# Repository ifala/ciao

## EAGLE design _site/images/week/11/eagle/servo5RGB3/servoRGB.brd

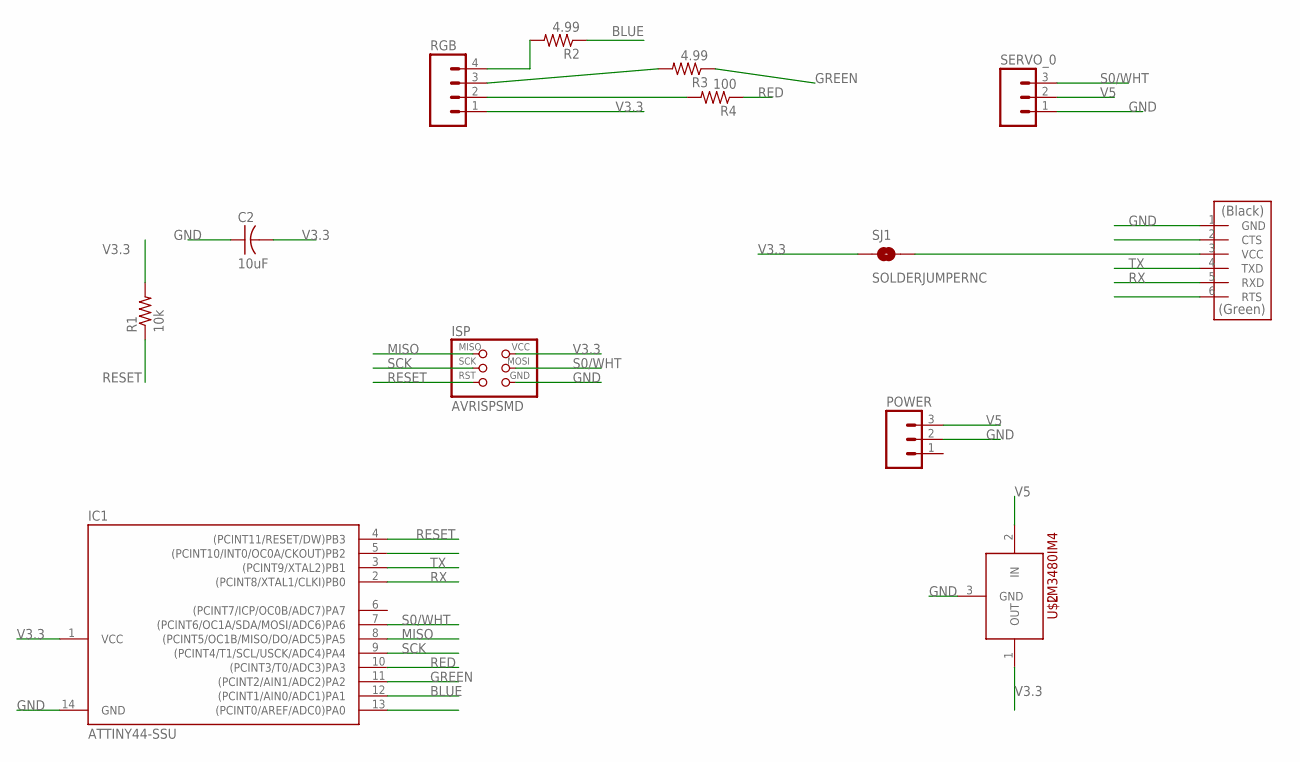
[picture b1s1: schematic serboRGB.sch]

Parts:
C2: 10uF; C1206FAB
IC1: ATTINY44-SSU; SOIC14
ISP: AVRISPSMD; 2X03SMD
POWER: M03SMD_RA_MALE_POST; 1X03_SMD_RA_MALE_POST
R1: 10k; 1206
R2, R3: 4.99; 1206
R4: 100; 1206
RGB: M04SMD; 1X04-SMD
SERVO_0: M03SMD_RA_MALE_POST; 1X03_SMD_RA_MALE_POST
SJ1: SOLDERJUMPERNC; SJ_2S
U$1: FTDI-SMD-HEADER; 1X06SMD
U$2: LM3480IM4; SOT23-3

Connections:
BLUE: IC1.12 ((PCINT1/AIN0/ADC1)PA1), R2.1
GND: C2.1, IC1.14 (GND), ISP.6 (GND), POWER.2, SERVO_0.1, U$1.1 (GND), U$2.3 (GND)
GREEN: IC1.11 ((PCINT2/AIN1/ADC2)PA2), R3.1
MISO: IC1.8 ((PCINT5/OC1B/MISO/DO/ADC5)PA5), ISP.1 (MISO)
unnamed: R4.2, RGB.2
unnamed: R3.2, RGB.3
unnamed: R2.2, RGB.4
unnamed: SJ1.2, U$1.3 (VCC)
RED: IC1.10 ((PCINT3/T0/ADC3)PA3), R4.1
RESET: IC1.4 ((PCINT11/RESET/DW)PB3), ISP.5 (RST), R1.1
RX: IC1.2 ((PCINT8/XTAL1/CLKI)PB0), U$1.5 (RXD)
S0/WHT: IC1.7 ((PCINT6/OC1A/SDA/MOSI/ADC6)PA6), ISP.4 (MOSI), SERVO_0.3
SCK: IC1.9 ((PCINT4/T1/SCL/USCK/ADC4)PA4), ISP.3 (SCK)
TX: IC1.3 ((PCINT9/XTAL2)PB1), U$1.4 (TXD)
V3.3: C2.2, IC1.1 (VCC), ISP.2 (VCC), R1.2, RGB.1, SJ1.1, U$2.1 (OUT)
V5: POWER.3, SERVO_0.2, U$2.2 (IN)

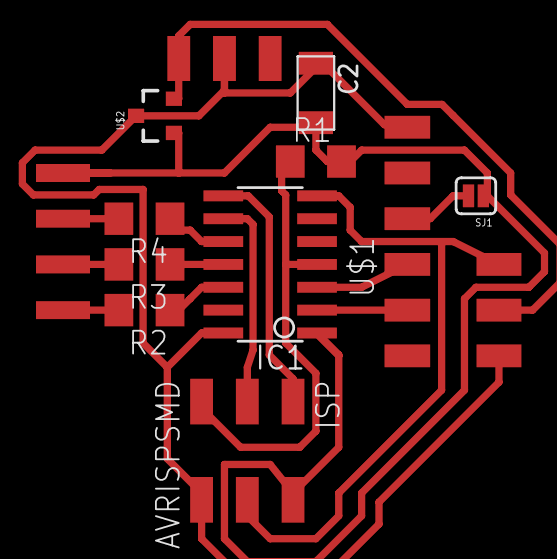
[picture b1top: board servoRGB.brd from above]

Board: 2 copper layers, 13 parts (0 on the bottom side), 16 nets.

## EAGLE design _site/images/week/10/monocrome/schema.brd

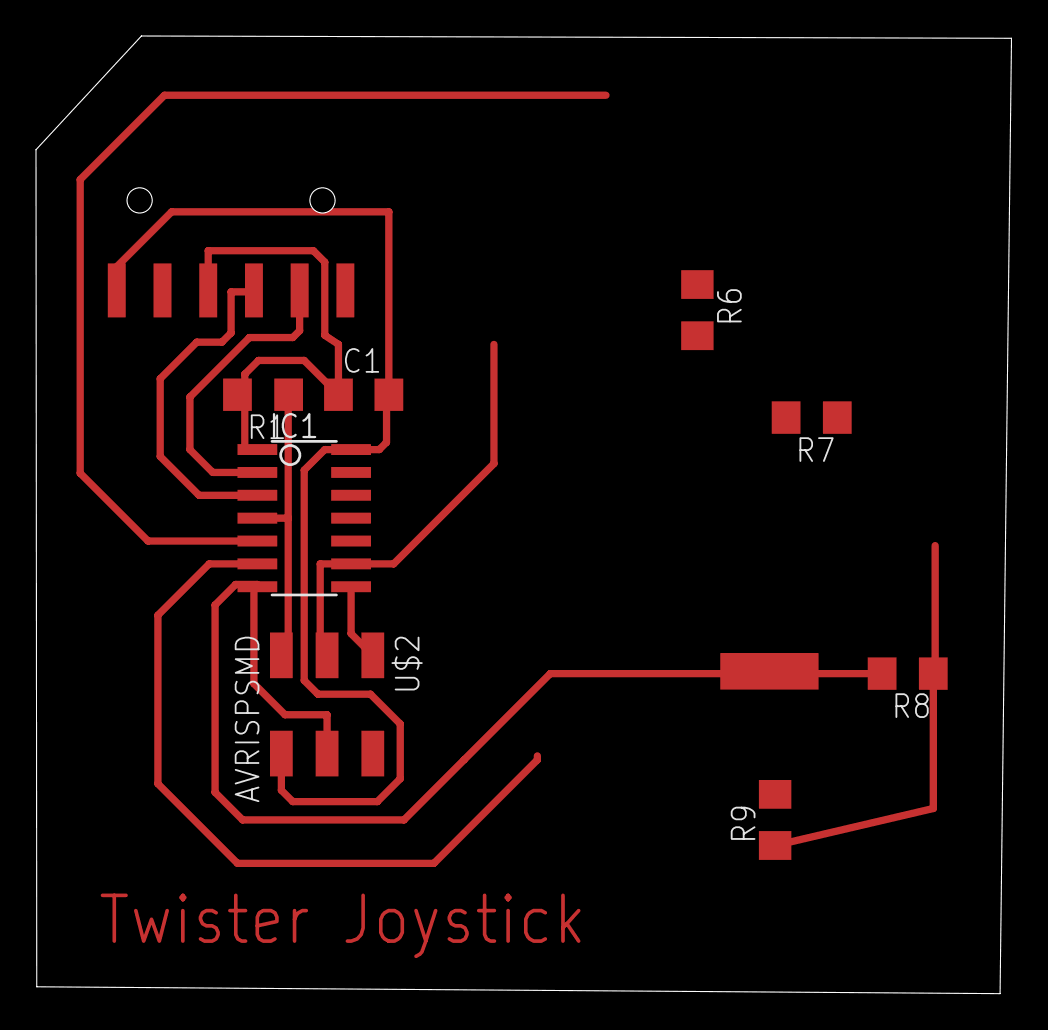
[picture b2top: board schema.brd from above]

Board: 1 copper layer, 54.2 x 53.2 mm, 9 parts (0 on the bottom side), 10 nets.

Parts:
C1: 1uf; C1206
IC1: ATTINY44-SSU; SOIC14
JP1: 1X06-SMD
R1: 10k; R1206
R6, R7, R8, R9: 1M; 1206
U$2: AVRISPSMD; 2X03SMD

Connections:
GND: C1.2, IC1.14, JP1.6, U$2.6
PAD4/SCK: IC1.9, R6.2, U$2.3
PAD5/MISO: IC1.8, R7.2, U$2.1
PAD6/MOSI: IC1.7, R8.2, U$2.4
PAD7: IC1.6, R9.2
RST: IC1.4, R1.1, U$2.5
RX: IC1.2, JP1.2
STEP: IC1.5, R6.1, R7.1, R8.1, R9.1
TX: IC1.3, JP1.3
VCC: C1.1, IC1.1, JP1.4, R1.2

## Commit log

2015-02-10 sito
2015-02-11 add week2
2015-02-11 add illustrator - week2
2015-02-17 news
2015-02-17 localhostremove
2015-02-17 add week3 file
2015-02-17 english
2015-02-19 add start week 4 - mod template
2015-02-19 correct link
2015-02-19 kk mod mobile
2015-02-19 cell
2015-02-24 week 4
2015-02-24 pond - solder
2015-02-24 code indent
2015-02-24 week4 rev1
2015-02-24 week 4 img rsz
2015-03-03 week5 _part1
2015-03-03 week 5 _ 2
2015-03-03 week 5 - update 3
2015-03-04 week 5 up4
2015-03-04 week5 up5
2015-03-10 week 6 update 1
2015-03-10 week 6 update 2
2015-03-10 week 6 update 3
2015-03-10 config
2015-03-18 week 7 _up1
2015-03-18 week 7 up2
2015-03-18 week7 up3
2015-03-18 week 7 up4
2015-03-19 week 7 up5
2015-03-19 week 7 up6
2015-03-19 week 7 up7
2015-03-19 _config error instagram
2015-03-19 correct link week6
2015-03-19 conclusion week7
2015-03-20 week 7 correction
2015-03-24 week 8 up1
2015-03-24 week8 up2
2015-03-25 week8 up3
2015-03-25 add file week 8
2015-03-30 update older assignment
2015-04-01 add google analytics
2015-04-01 revision week1
2015-04-01 revision week1 up2
2015-04-01 week4 up1
2015-04-03 since week8 update
2015-04-06 update link
2015-04-06 update1 week9
2015-04-07 up2 week9
2015-04-07 up3 week9
2015-04-07 up4 week9
2015-04-07 up5 week9
2015-04-07 up6 week9
2015-04-14 update 10
2015-04-15 update index
2015-04-21 week 10 up2
    add postUPD.html mod
2015-04-21 week 10 up3
2015-04-21 week 10 up4
2015-04-21 week 10 up5
2015-04-21 week 10 up6
2015-04-21 week 11 up1
2015-04-21 week 10 up7 tr correction
    thanks teresa!
2015-04-22 week 11 up1o
2015-04-22 week 11 up3
2015-04-29 week 11 up4
2015-04-29 week 11 up5
2015-04-29 week 11 up6
2015-04-29 week 11 up7
2015-05-09 Up13 e 14
2015-05-12 week15
2015-05-12 15-2
2015-05-12 14-3
2015-05-12 14-4
2015-05-13 14-5
2015-05-13 14-6
2015-05-13 12-13
2015-05-18 week 15-1
2015-05-20 15-4
2015-05-20 15-5
2015-05-20 15-6
2015-05-20 fp-1
2015-05-20 fp-2
2015-05-20 fp-4
2015-05-27 servo_page
2015-06-02 presentation
2015-06-08 presentation.png-html
2015-06-08 video file presentation
2015-06-22 final_update_1
2015-06-24 final_update_2
2015-06-26 final_update_3
2015-06-27 final_update_4
2015-06-27 final_update_4_1
2015-06-27 final_update_4_2
2015-06-27 final_update_4_3
2021-03-04 Update from Forestry.io - Updated Forestry configuration

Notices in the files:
parts and their libraries:
SparkFun-Connectors: Licensing: Creative Commons ShareAlike 4.0 International - https://creativecommons.org/licenses/by-sa/4.0
